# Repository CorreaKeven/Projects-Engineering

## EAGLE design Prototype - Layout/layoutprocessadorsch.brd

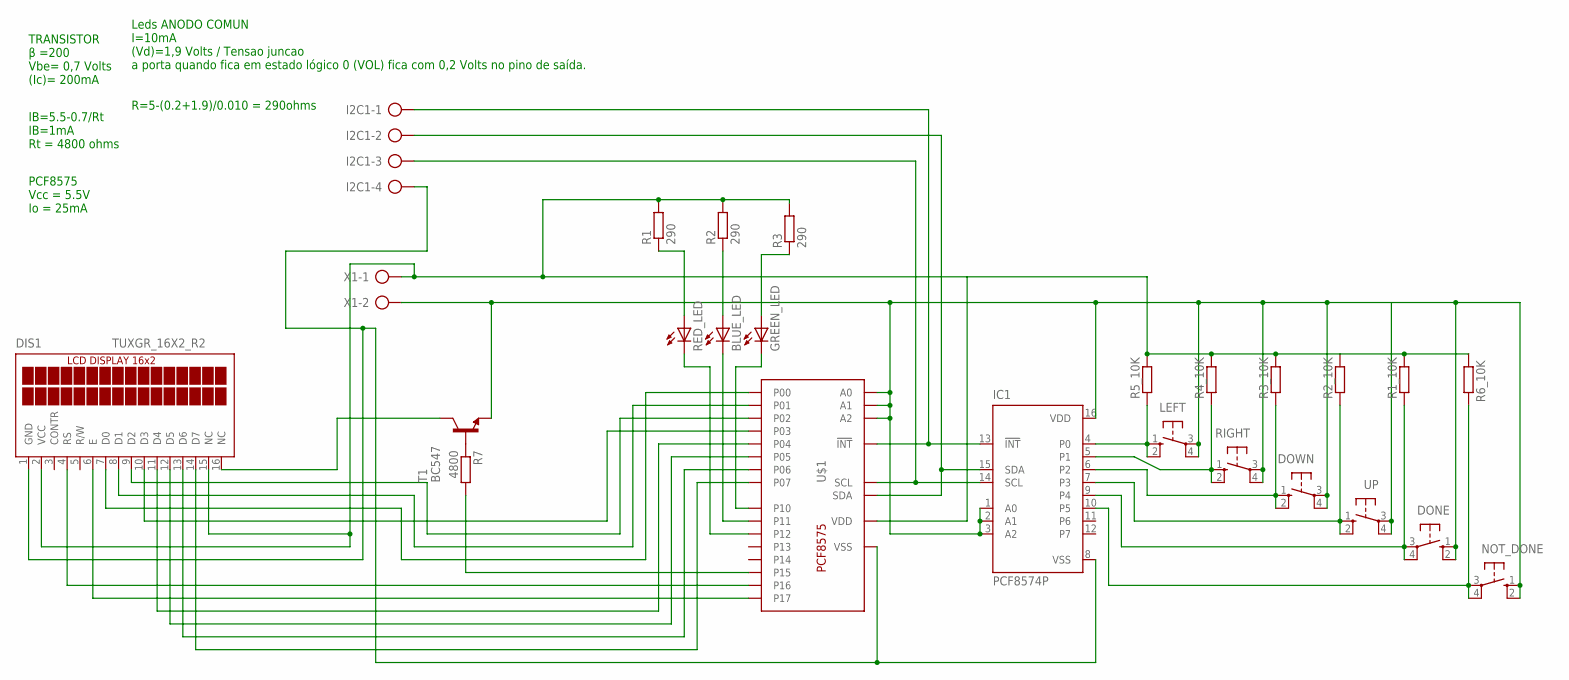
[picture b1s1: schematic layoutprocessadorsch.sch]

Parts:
BLUE_LED: LED5MM
DIS1: TUXGR_16X2_R2
DONE: 10-XX; B3F-10XX
DOWN: 10-XX; B3F-10XX
GREEN_LED: LED5MM
I2C1: AK500/4-H
IC1: PCF8574P; DIL16
LEFT: 10-XX; B3F-10XX
NOT_DONE: 10-XX; B3F-10XX
R1, R2, R3: 290; 0207/7
R1_10K, R2_10K, R3_10K, R4_10K, R5_10K, R6_10K: R-EU_0207/7; 0207/7
R7: 4800; 0207/7
RED_LED: LED5MM
RIGHT: 10-XX; B3F-10XX
T1: BC547; TO92
U$1: PCF8575C; SOP24
UP: 10-XX; B3F-10XX
X1: AK500/2-H

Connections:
unnamed: DIS1.14 (D7), U$1.P$11 (P07)
unnamed: R7.1, T1.2 (B)
unnamed: I2C1.1, IC1.13 (!INT), U$1.P$1 (!INT)
unnamed: I2C1.2, IC1.15 (SDA), U$1.P$23 (SDA)
unnamed: DIS1.7 (D0), U$1.P$4 (P00)
unnamed: DIS1.8 (D1), U$1.P$5 (P01)
unnamed: DIS1.9 (D2), U$1.P$6 (P02)
unnamed: DIS1.10 (D3), U$1.P$7 (P03)
unnamed: DIS1.1 (GND), I2C1.4, IC1.8 (VSS), U$1.P$12 (VSS)
unnamed: DIS1.6 (E), U$1.P$20 (P17)
unnamed: DIS1.4 (RS), U$1.P$19 (P16)
unnamed: I2C1.3, IC1.14 (SCL), U$1.P$22 (SCL)
unnamed: DIS1.11 (D4), U$1.P$8 (P04)
unnamed: DIS1.12 (D5), U$1.P$9 (P05)
unnamed: DIS1.13 (D6), U$1.P$10 (P06)
unnamed: R7.2, U$1.P$18 (P15)
unnamed: DIS1.16 (NC), T1.3 (C)
unnamed: GREEN_LED.K (C), U$1.P$13 (P10)
unnamed: IC1.4 (P0), LEFT.1 (S), LEFT.2 (S1), R5_10K.1
unnamed: IC1.5 (P1), R4_10K.1, RIGHT.1 (S), RIGHT.2 (S1)
unnamed: DOWN.1 (S), DOWN.2 (S1), IC1.6 (P2), R3_10K.1
unnamed: DIS1.2 (VCC), DIS1.15 (NC), R1.2, R1_10K.2, R2.2, R2_10K.2, R3.2, R3_10K.2, R4_10K.2, R5_10K.2, R6_10K.1, U$1.P$24 (VDD), X1.1
unnamed: DONE.3, DONE.4 (P1), IC1.9 (P4), R1_10K.1
unnamed: IC1.10 (P5), NOT_DONE.3, NOT_DONE.4 (P1), R6_10K.2
unnamed: IC1.7 (P3), R2_10K.1, UP.1 (S), UP.2 (S1)
unnamed: BLUE_LED.K (C), U$1.P$14 (P11)
unnamed: RED_LED.K (C), U$1.P$15 (P12)
unnamed: R1.1, RED_LED.A
unnamed: BLUE_LED.A, R2.1
unnamed: GREEN_LED.A, R3.1
unnamed: DONE.1 (S), DONE.2 (S1), DOWN.3, DOWN.4 (P1), IC1.1 (A0), IC1.2 (A1), IC1.3 (A2), IC1.16 (VDD), LEFT.3, LEFT.4 (P1), NOT_DONE.1 (S), NOT_DONE.2 (S1), RIGHT.3, RIGHT.4 (P1), T1.1 (E), U$1.P$2 (A1), U$1.P$3 (A2), U$1.P$21 (A0), UP.3, UP.4 (P1), X1.2

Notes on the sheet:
TRANSISTOR β =200 Vbe= 0,7 Volts (Ic)= 200mA
Leds ANODO COMUN I=10mA (Vd)=1,9 Volts / Tensao juncao a porta quando fica em estado lógico 0 (VOL) fica com 0,2 Volts no pino de saída. R=5-(0.2+1.9)/0.010 = 290ohms
PCF8575 Vcc = 5.5V Io = 25mA
IB=5.5-0.7/Rt IB=1mA Rt = 4800 ohms

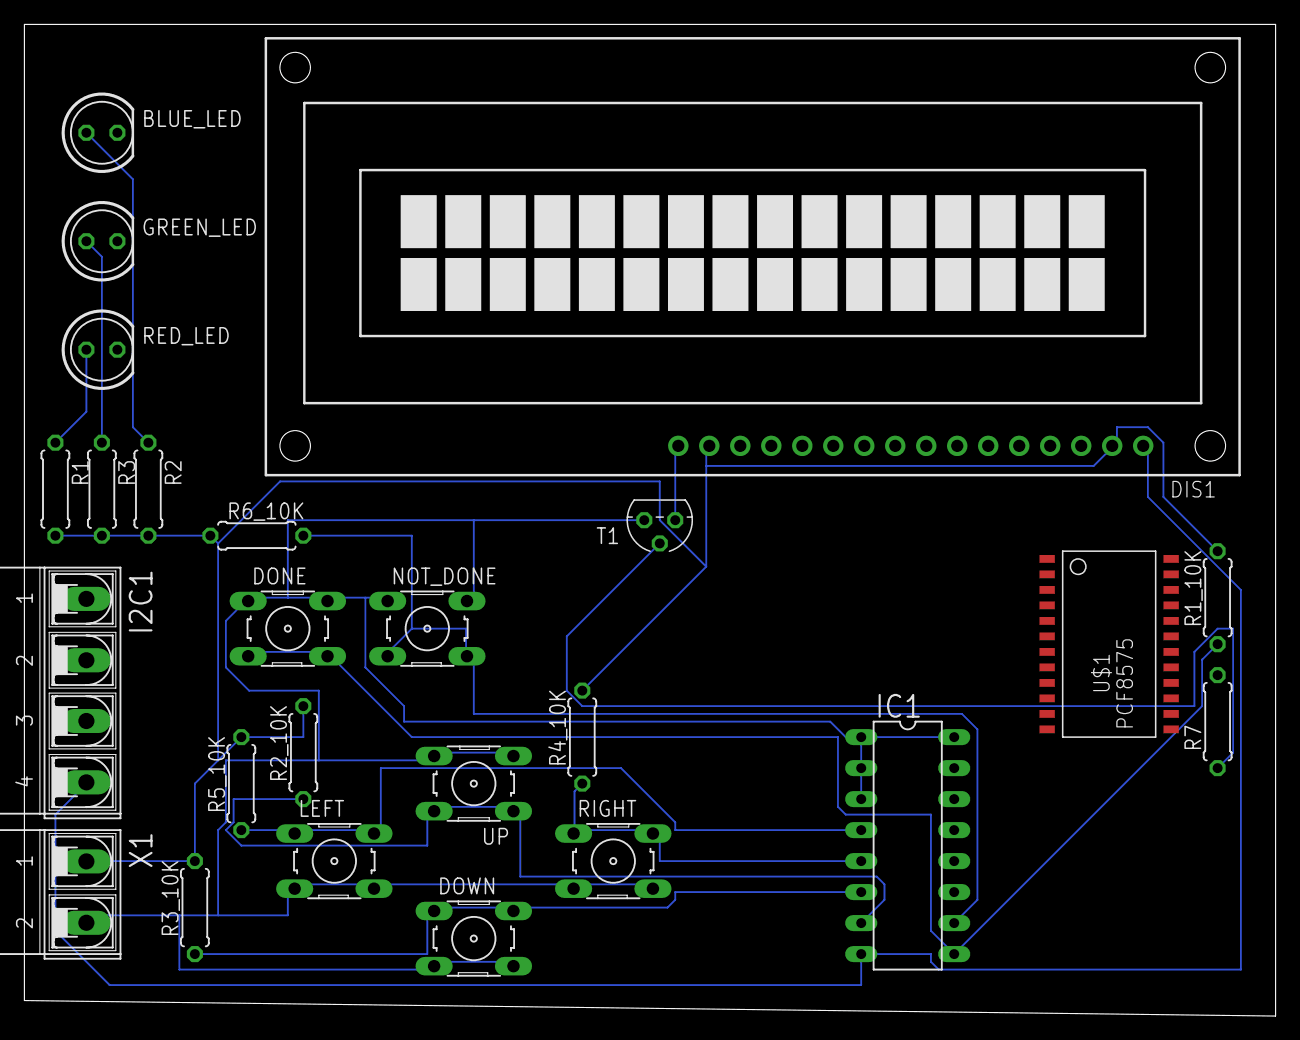
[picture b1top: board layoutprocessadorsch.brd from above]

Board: 2 copper layers, 102.5 x 81.3 mm, 25 parts (0 on the bottom side), 31 nets.

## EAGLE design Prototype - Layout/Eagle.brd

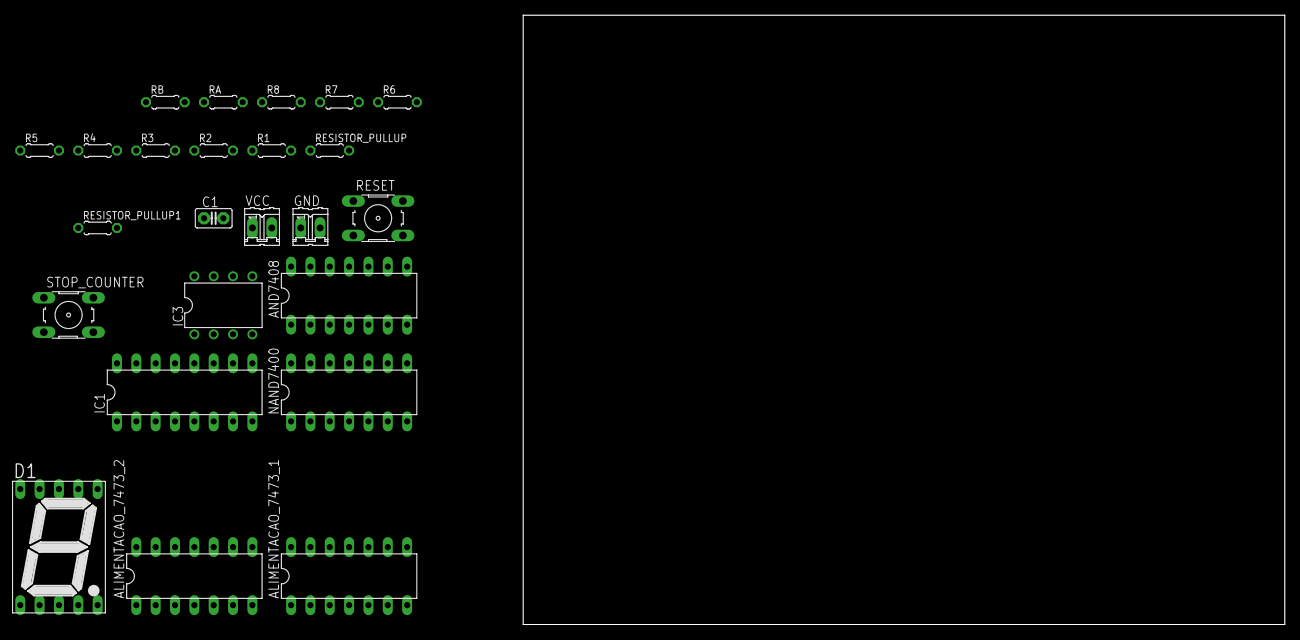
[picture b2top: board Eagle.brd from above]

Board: 2 copper layers, 100.0 x 80.0 mm, 24 parts (0 on the bottom side), 29 nets, no tracks yet.

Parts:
ALIMENTACAO_7473_1, ALIMENTACAO_7473_2: 74LS73N; DIL14
AND7408: 7408N; DIL14
C1: 10µF; C2.5-2
D1: 7SEG-13
GND: 02P
IC1: 74LS47N; DIL16
IC3: LM555N; DIL08
NAND7400: 7400N; DIL14
R1, R2, R3, R4, R5, R6, R7: 220; 0204/5
R8: 1k; 0204/5
RA: 6k8; 0204/5
RB: 33k; 0204/5
RESET: B3F-10XX
RESISTOR_PULLUP, RESISTOR_PULLUP1: 1k; 0204/5
STOP_COUNTER: B3F-10XX
VCC: 02P

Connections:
unnamed: IC3.7, RA.1, RB.2
unnamed: C1.2, IC3.2, IC3.6, RB.1
unnamed: AND7408.9, RESET.1, RESET.2, RESISTOR_PULLUP1.1
unnamed: ALIMENTACAO_7473_1.11, ALIMENTACAO_7473_2.11, AND7408.7, C1.1, GND.1, GND.2, IC1.8, IC3.1, NAND7400.7, RESET.3, RESET.4, STOP_COUNTER.1, STOP_COUNTER.2
unnamed: AND7408.1, IC3.3
unnamed: ALIMENTACAO_7473_1.1, AND7408.3
unnamed: ALIMENTACAO_7473_1.5, ALIMENTACAO_7473_1.12, IC1.7
unnamed: ALIMENTACAO_7473_1.9, ALIMENTACAO_7473_2.1, IC1.1, NAND7400.2
unnamed: ALIMENTACAO_7473_2.5, ALIMENTACAO_7473_2.12, IC1.2
unnamed: AND7408.2, RESISTOR_PULLUP.1, STOP_COUNTER.3, STOP_COUNTER.4
unnamed: AND7408.10, NAND7400.3
unnamed: ALIMENTACAO_7473_2.9, IC1.6, NAND7400.1
unnamed: IC1.13, R1.1
unnamed: ALIMENTACAO_7473_1.2, ALIMENTACAO_7473_1.6, ALIMENTACAO_7473_2.2, ALIMENTACAO_7473_2.6, AND7408.8
unnamed: IC1.12, R2.1
unnamed: IC1.11, R3.1
unnamed: IC1.10, R4.1
unnamed: IC1.9, R5.1
unnamed: IC1.15, R6.1
unnamed: IC1.14, R7.1
unnamed: D1.7, R1.2
unnamed: D1.6, R2.2
unnamed: D1.4, R3.2
unnamed: D1.2, R4.2
unnamed: D1.1, R5.2
unnamed: D1.9, R6.2
unnamed: D1.10, R7.2
unnamed: IC1.3, IC1.4, IC1.5, R8.2
unnamed: ALIMENTACAO_7473_1.3, ALIMENTACAO_7473_1.4, ALIMENTACAO_7473_1.7, ALIMENTACAO_7473_1.10, ALIMENTACAO_7473_1.14, ALIMENTACAO_7473_2.3, ALIMENTACAO_7473_2.4, ALIMENTACAO_7473_2.7, ALIMENTACAO_7473_2.10, ALIMENTACAO_7473_2.14, AND7408.14, D1.3, D1.8, IC1.16, IC3.4, IC3.8, NAND7400.14, R8.1, RA.2, RESISTOR_PULLUP.2, RESISTOR_PULLUP1.2, VCC.1, VCC.2
